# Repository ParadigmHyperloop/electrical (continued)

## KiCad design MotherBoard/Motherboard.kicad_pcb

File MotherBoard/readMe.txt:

Notes for Motherboard files.

*** Schematic ***
BBB headers will be shown true to pins because pinouts are not 
   set and updating the headers will be annoying.

Signals for MUX pins will be denoted with labels instead of wire 
   connections for flexibility and cleanliness.     

*** hyperLib ***
A and B designator for CD74HC4067 designate pinout orientation
   A is true to the physical pins, B is to show purpose/flow.

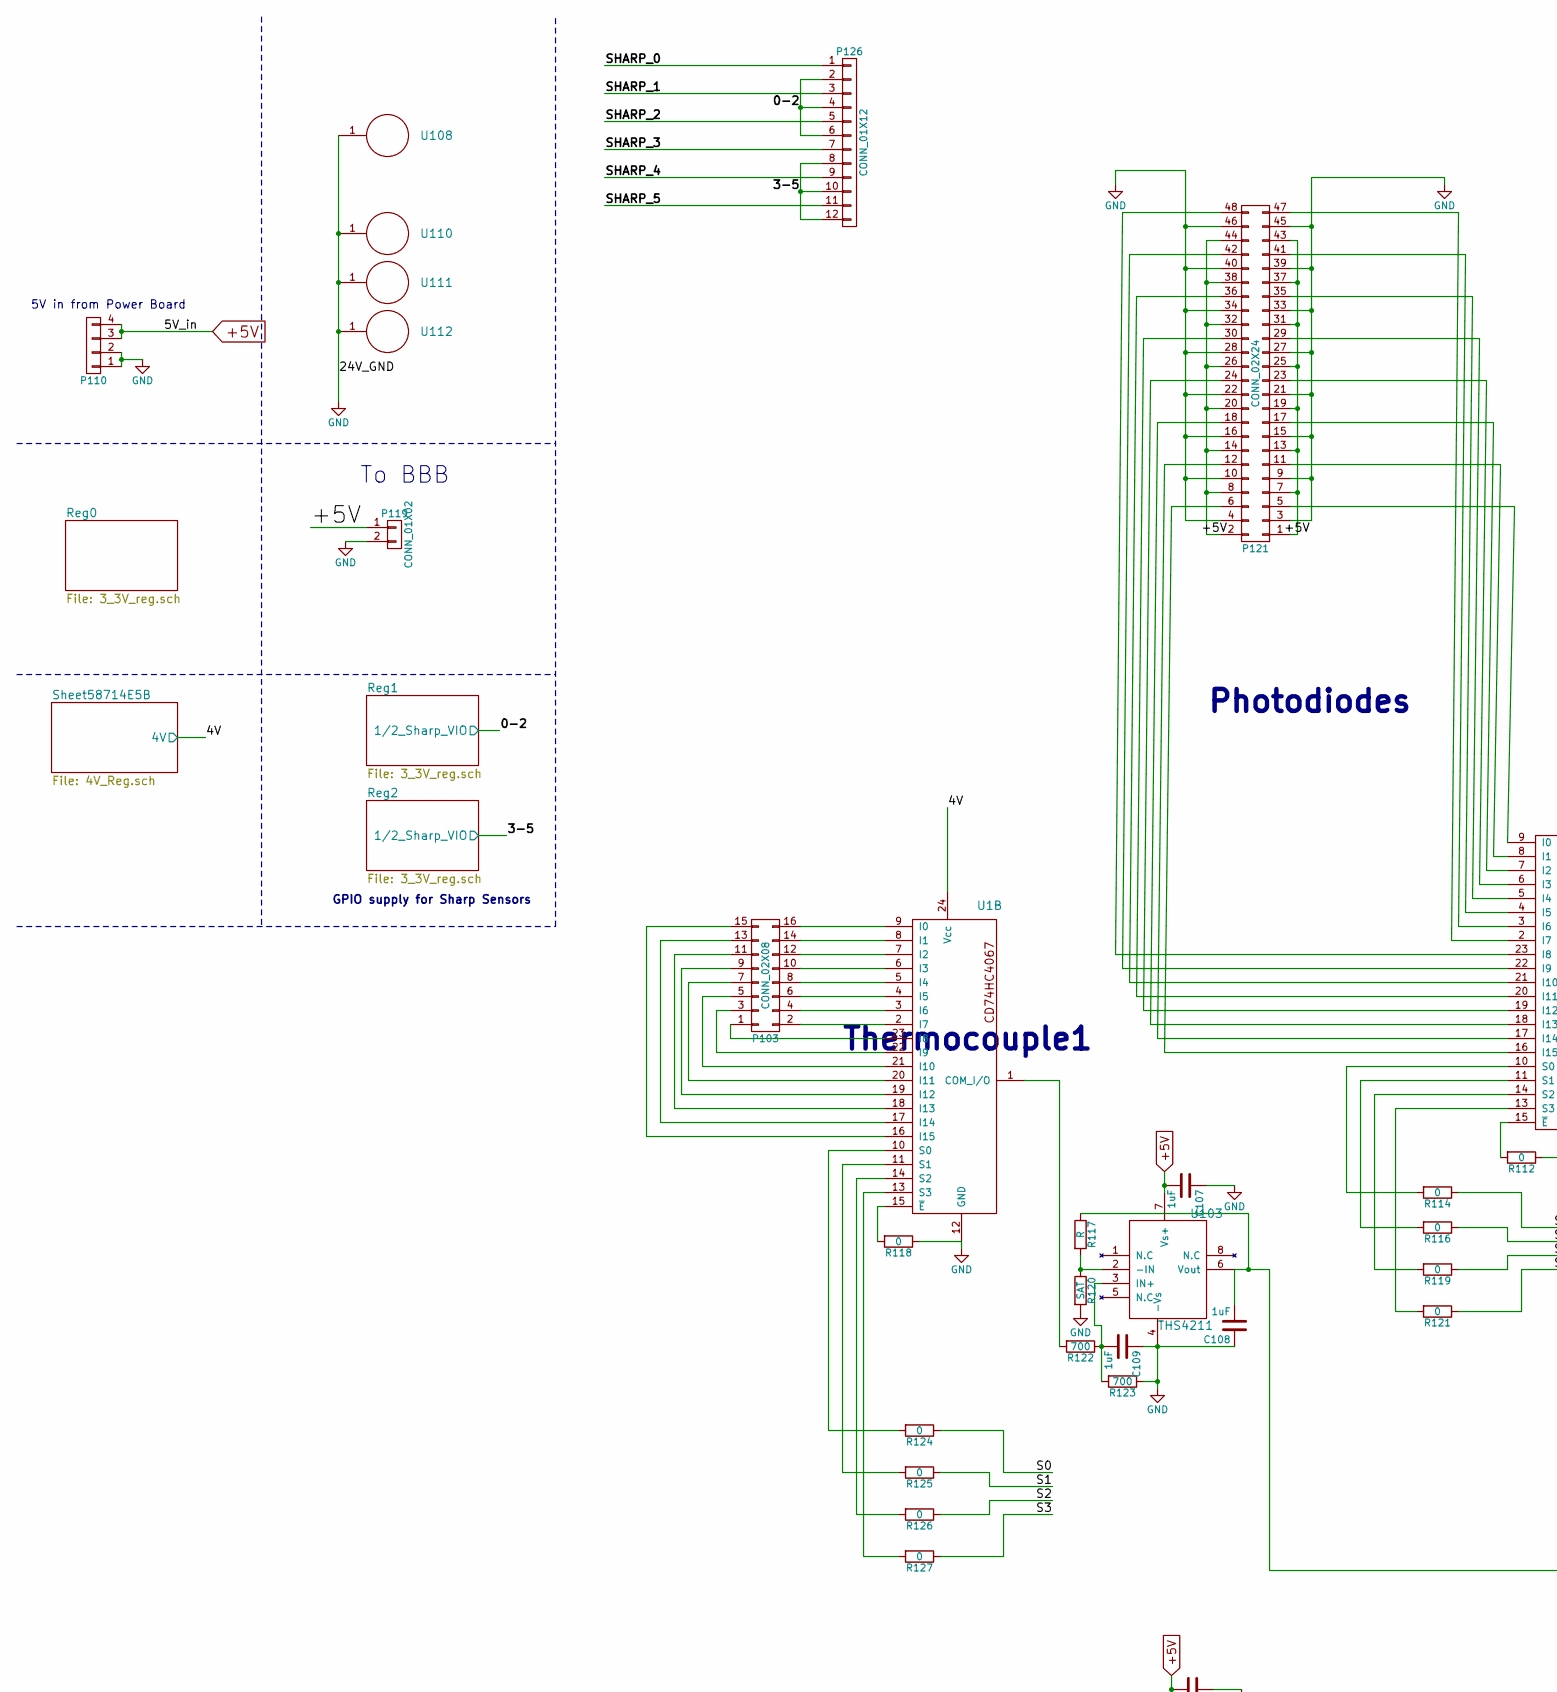
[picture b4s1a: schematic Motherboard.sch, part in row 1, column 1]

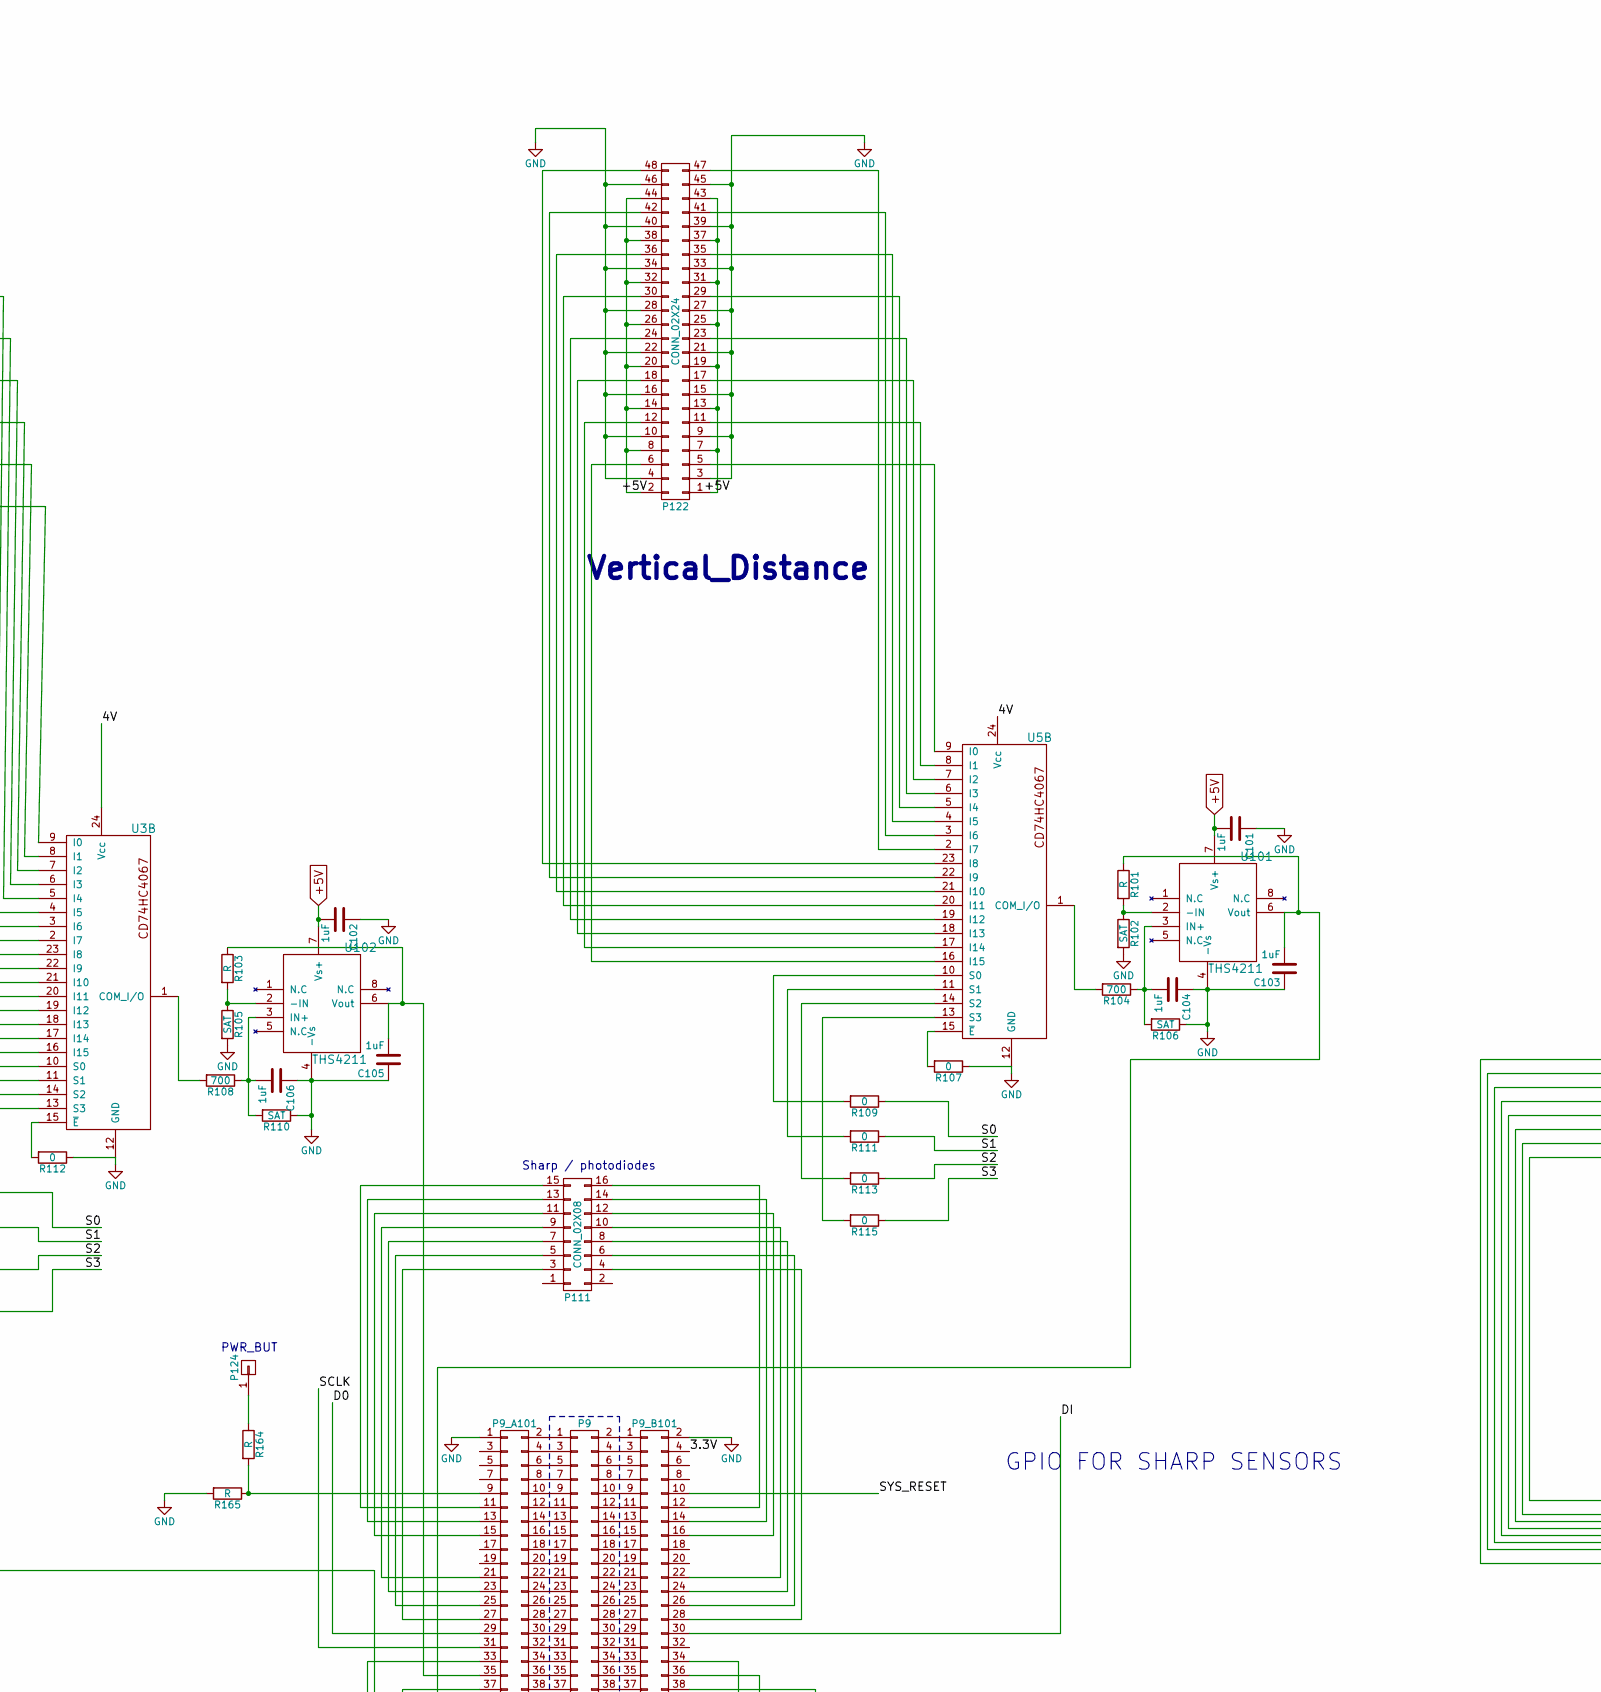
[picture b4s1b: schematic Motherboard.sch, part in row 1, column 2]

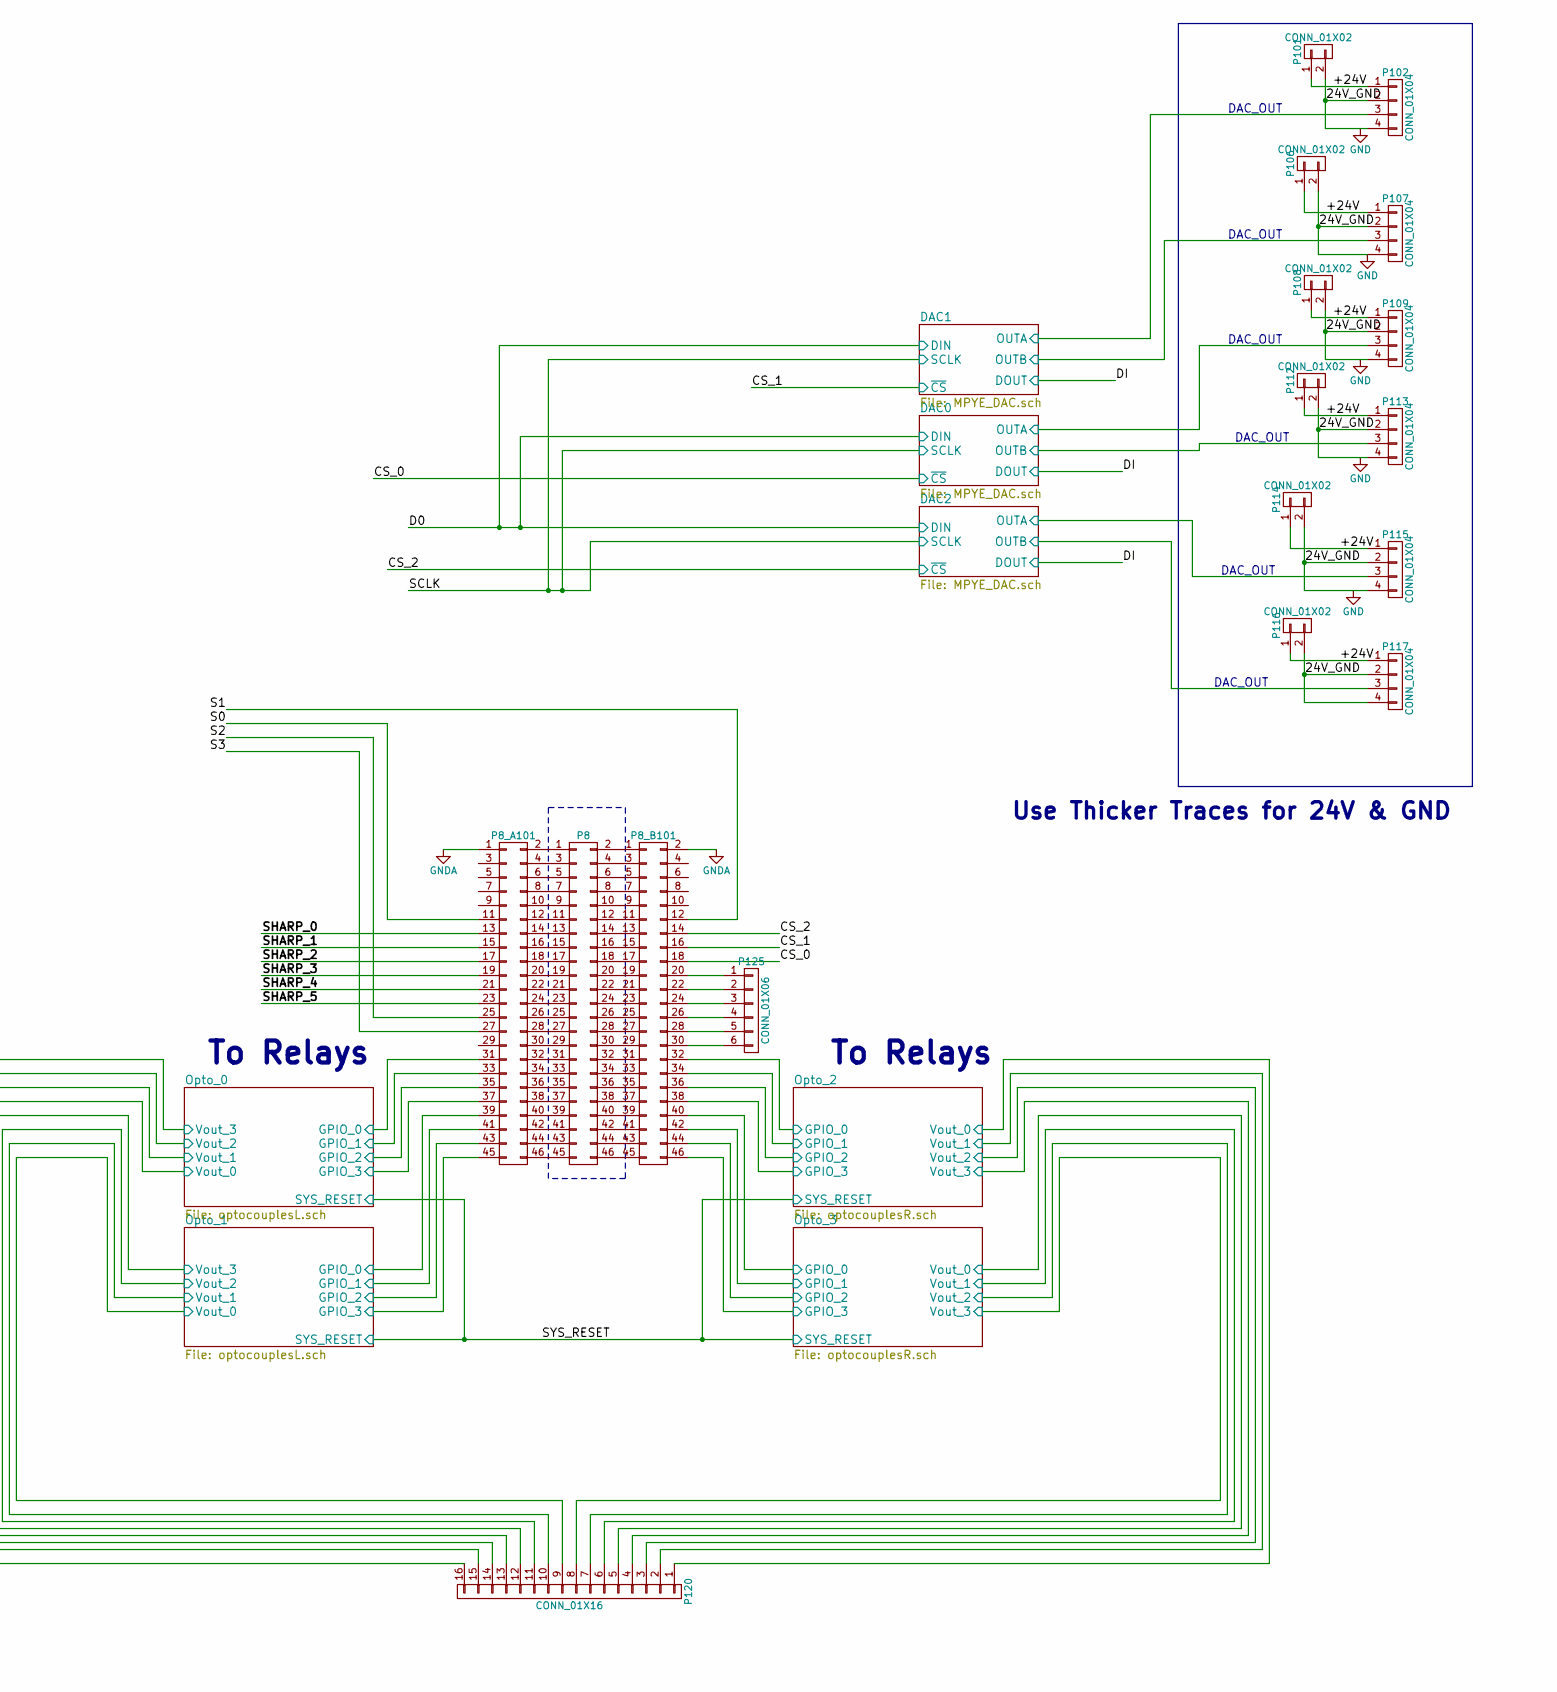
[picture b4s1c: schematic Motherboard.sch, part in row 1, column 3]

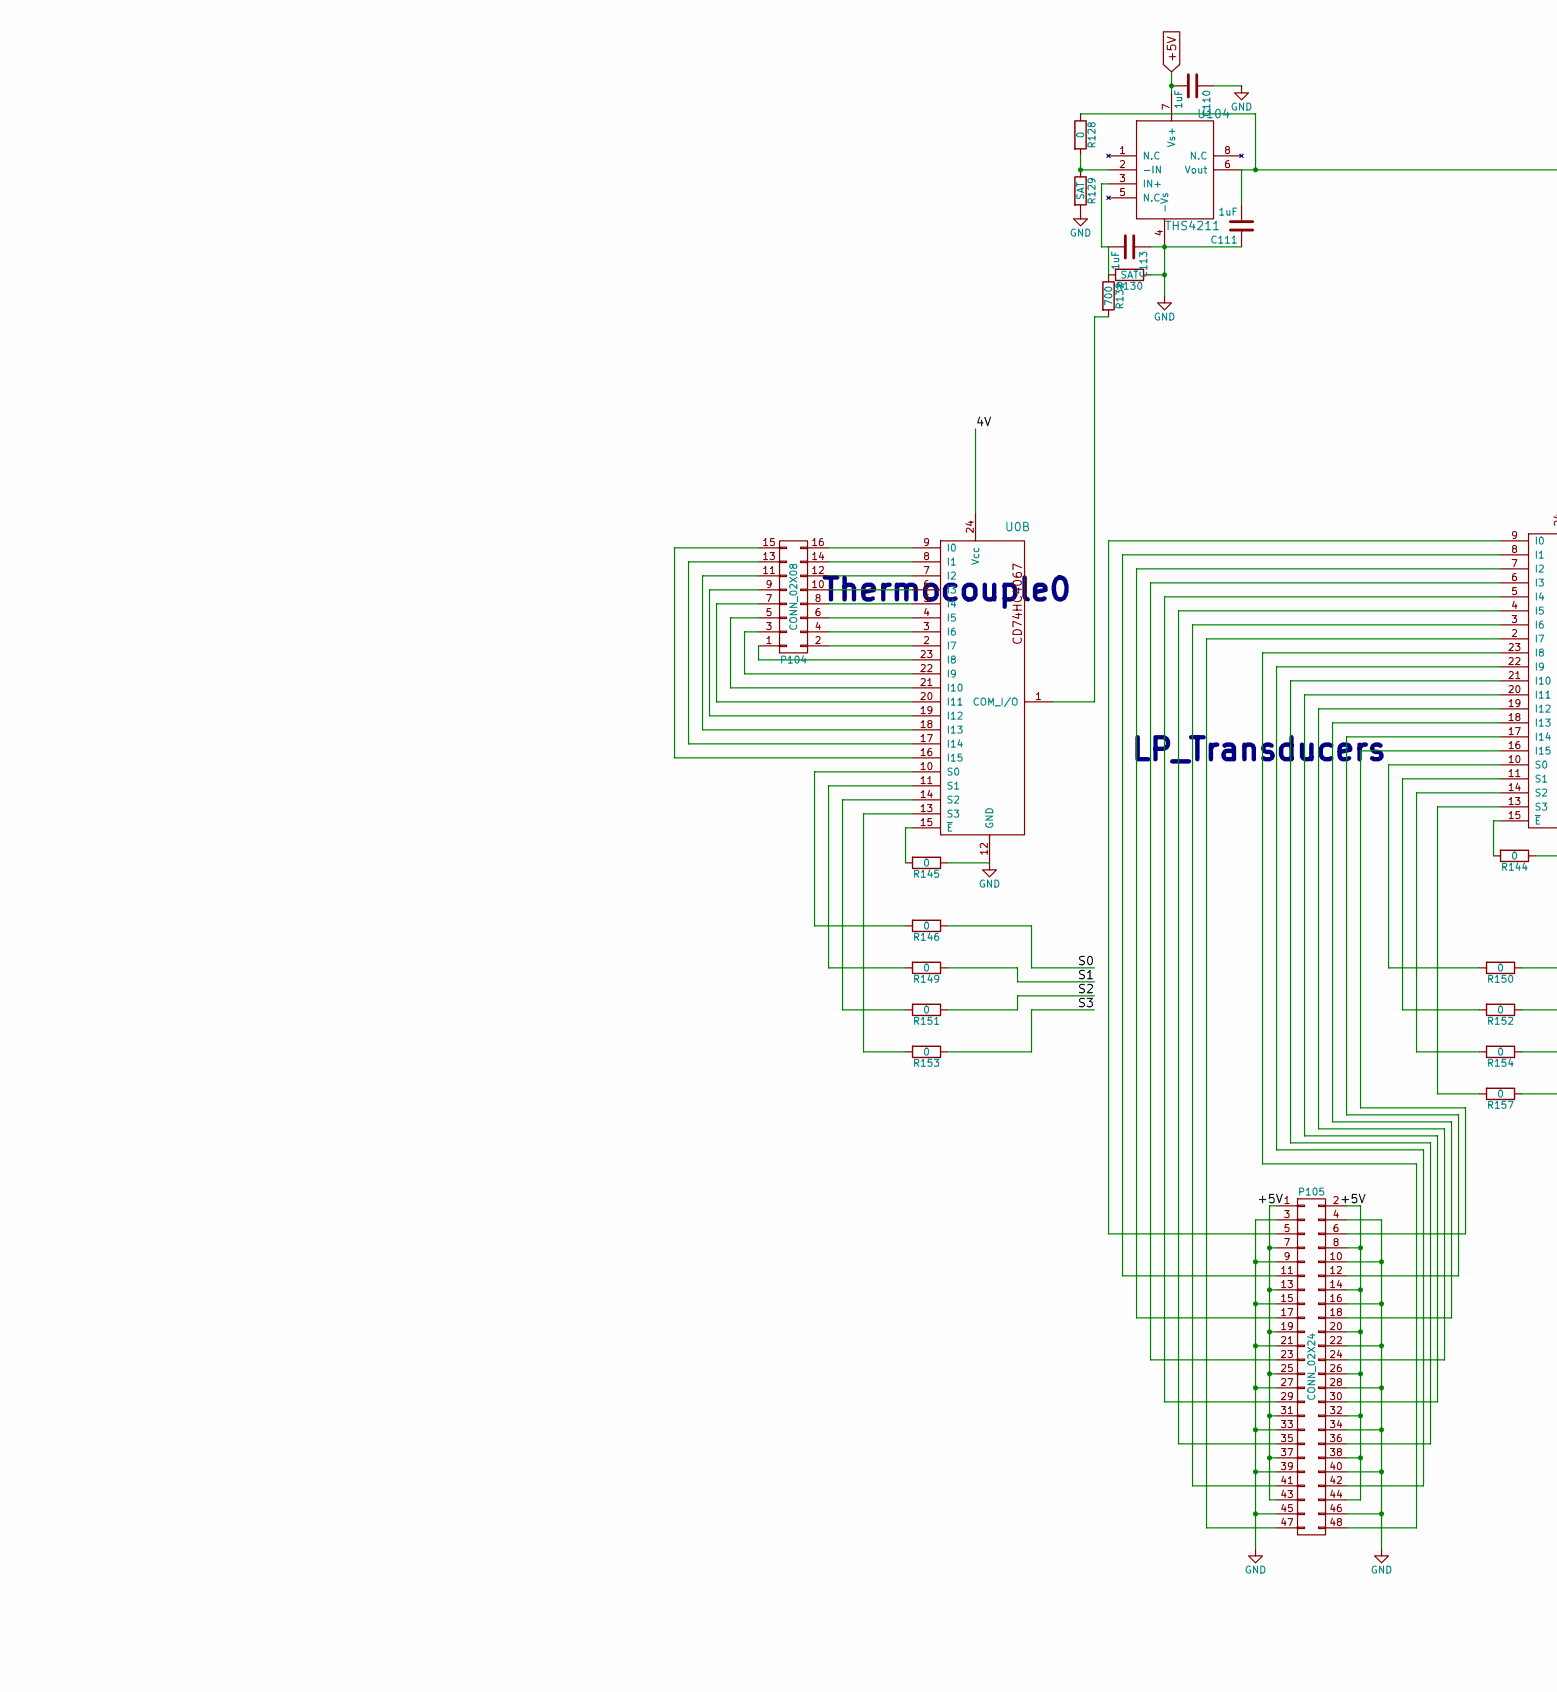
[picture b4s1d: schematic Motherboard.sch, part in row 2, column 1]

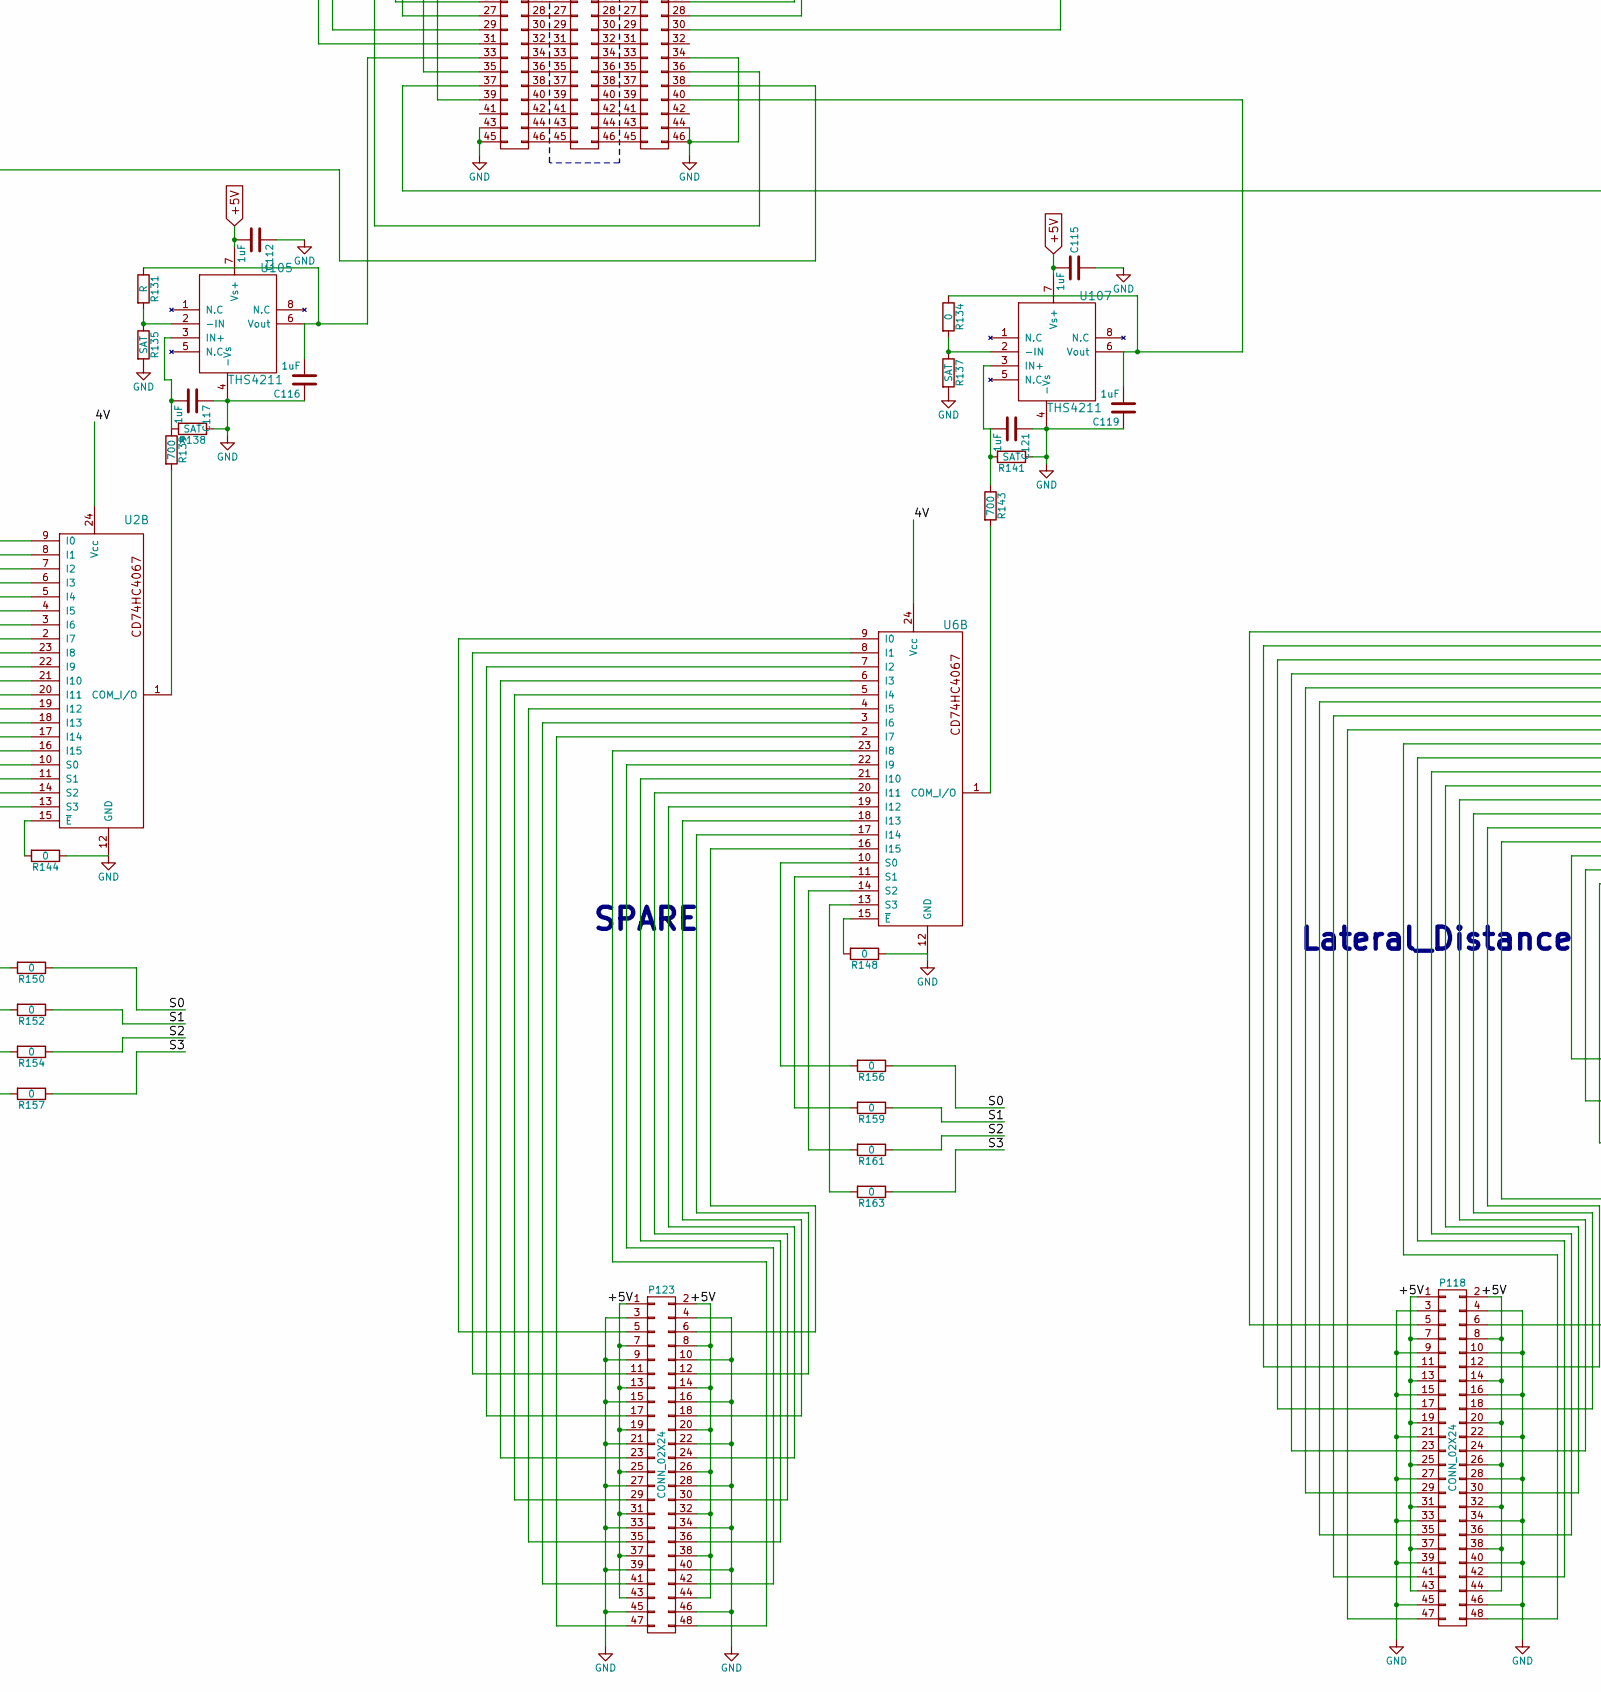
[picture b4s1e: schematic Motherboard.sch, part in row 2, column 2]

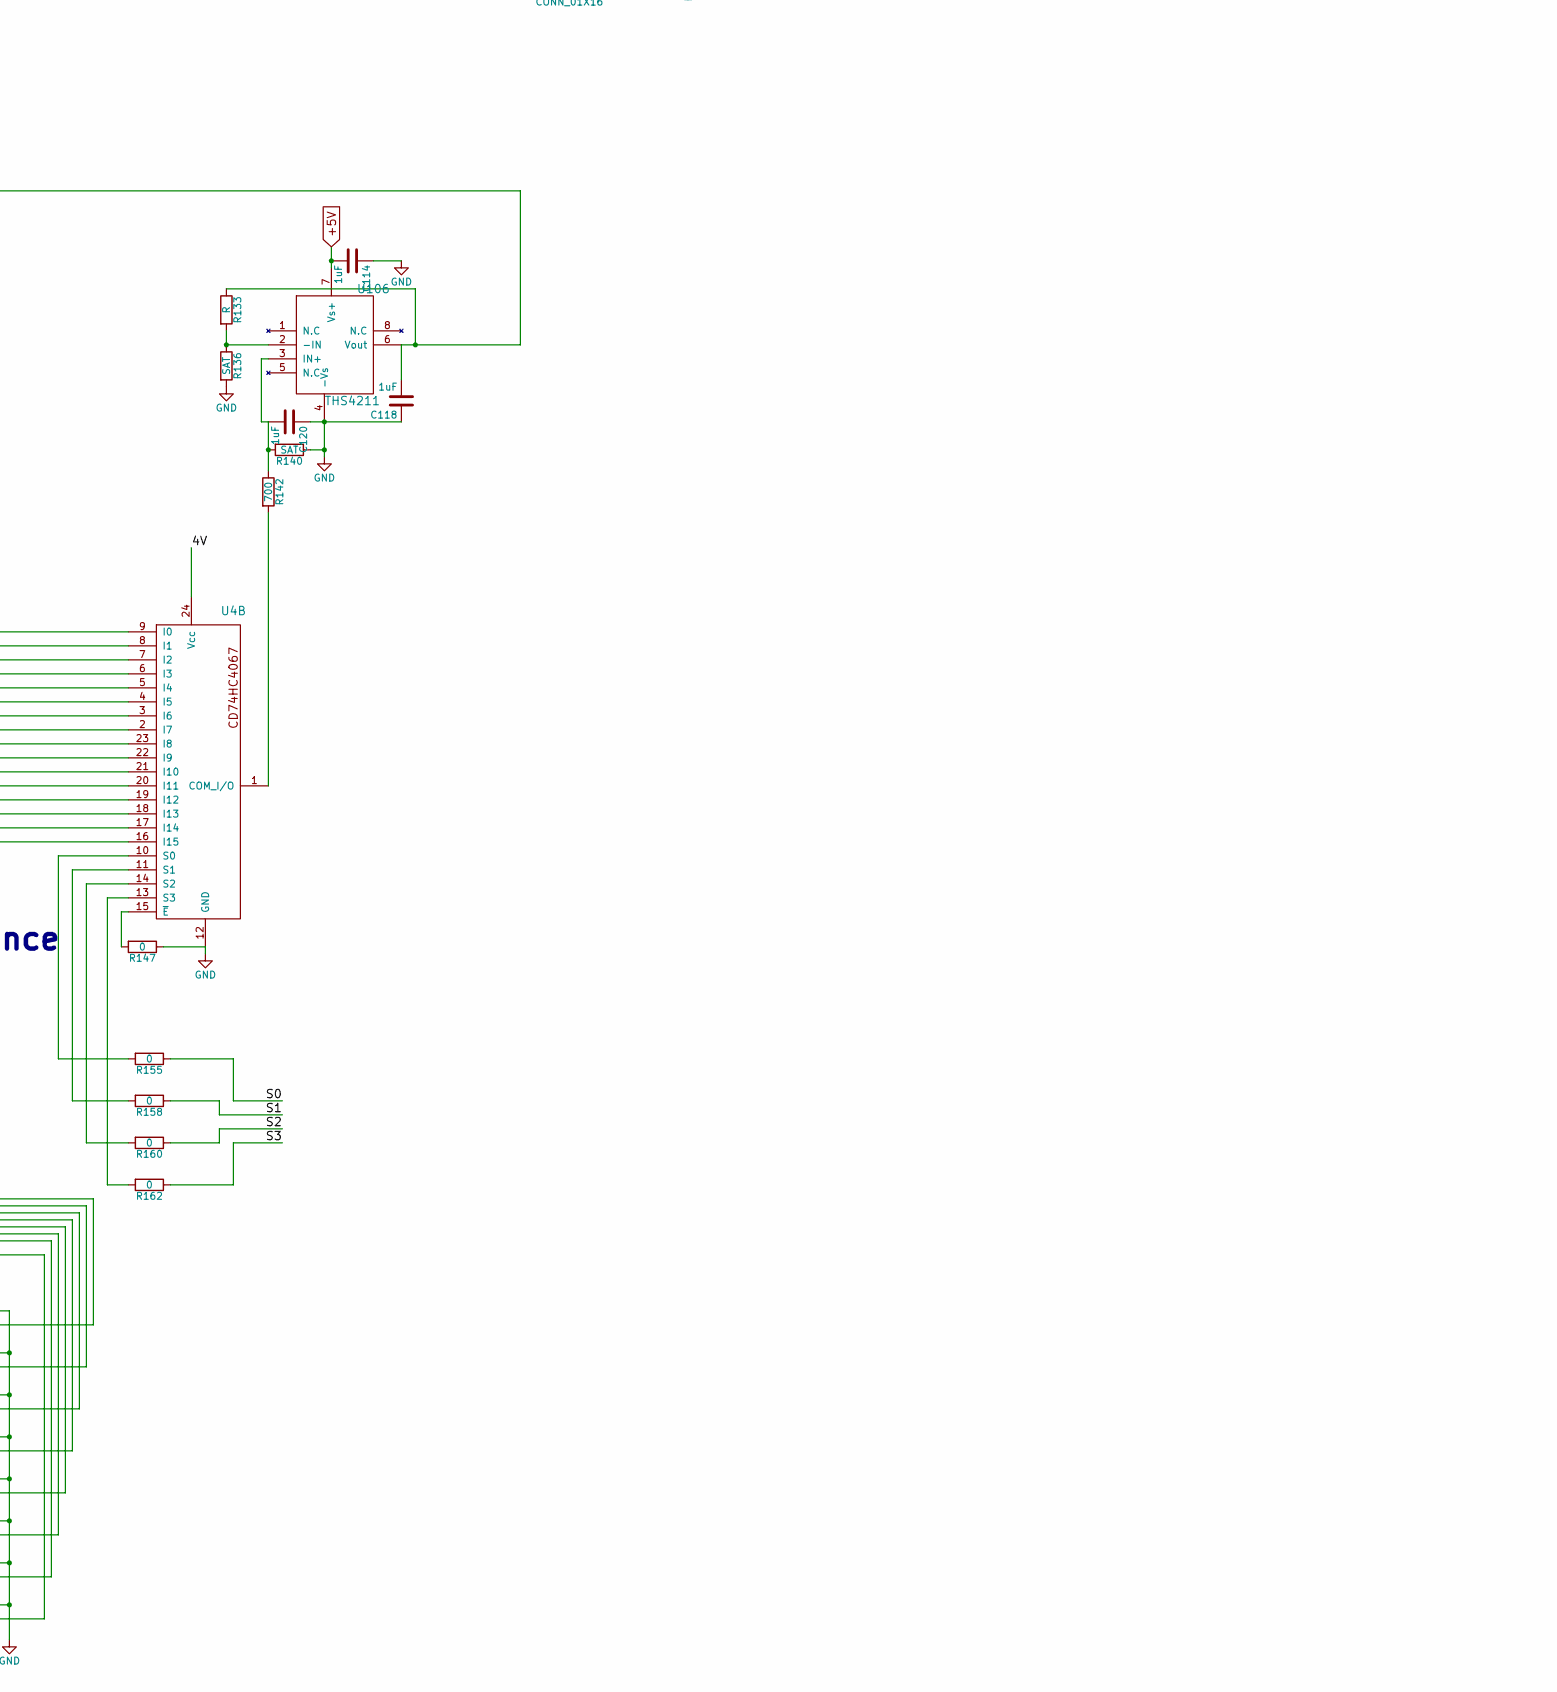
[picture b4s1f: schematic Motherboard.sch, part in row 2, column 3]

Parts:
C101, C102, C103, C104, C105, C106, C107, C108, C109, C110, C111, C112, C113, C114, C115, C116, C117, C118, C119, C120, C121: 1uF; C_0603_HandSoldering
P8, P8_A101, P8_B101: CONN_02X23; header_2.54x2.54mm_spacing_pinName
P9, P9_A101, P9_B101: CONN_02X23; header_2.54x2.54mm_spacing_pinName; Digikey P/N S2011E-23-ND
P101: CONN_01X02; TEconnectivity_2pin_screwTerminal; Digikey P/N A98333-ND
P102: CONN_01X04; pheonix_4pin_screwTerminal; Digikey P/N 277-1275-ND
P103, P104, P111: CONN_02X08; Molex_16pin_milliGrid; Digikey P/N WM18864-ND
P105, P118, P121, P122, P123: CONN_02X24; 02x48pin_2x2mm_Amphenol_header; Digikey P/N 609-2674-ND
P106, P108, P112, P114, P116: CONN_01X02; TEconnectivity_2pin_screwTerminal
P107: CONN_01X04; pheonix_4pin_screwTerminal; Digikey P/N 277-1275-Nd
P109, P110, P113, P115, P117: CONN_01X04; pheonix_4pin_screwTerminal
P119: CONN_01X02; SolderWirePad_2x_1mmDrill
P120: CONN_01X16; 16pin_screwTerminal; Digikey P/N 277-1733-ND
P124: CONN_01X01; 1pin
P125: CONN_01X06; CONN_01x06_standard
P126: CONN_01X12; 12pin_screwTerminal; Digikey P/N 277-1283-ND
R101, R103, R117, R131, R133, R164, R165: R; R_0603_HandSoldering
R102, R105, R106, R110, R120, R129, R130, R135, R136, R137, R138, R140, R141: SAT; R_0603_HandSoldering
R104, R108, R122, R123, R132, R139, R142, R143: 700; R_0603_HandSoldering
R107, R109, R111, R112, R113, R114, R115, R116, R118, R119, R121, R124, R125, R126, R127, R128, R134, R144, R145, R146, R147, R148, R149, R150, R151, R152, R153, R154, R155, R156, R157, R158, R159, R160, R161, R162, R163: 0; R_0603_HandSoldering
U0: CD74HC4067; SOIC-24W_7.5x15.4mm_Pitch1.27mm; Digikey P/N CD74HCT4067MG4-ND
U1, U2, U3, U4, U5, U6: CD74HC4067; SOIC-24W_7.5x15.4mm_Pitch1.27mm
U101, U102, U103, U104, U106, U107: THS4211; SOIC-8_3.9x4.9mm_Pitch1.27mm
U105: THS4211; SOIC-8_3.9x4.9mm_Pitch1.27mm; Digikey P/N 296-13790-5-ND
U108, U110, U111, U112: mounting_hole_5.5mm; MountingHole_5.5mm_Pad_Via

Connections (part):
/0-2: P126.2, P126.4, P126.6; also elsewhere on the board
/3-5: P126.8, P126.10, P126.12; also elsewhere on the board
/4V: U0.24 (Vcc), U1.24 (Vcc), U2.24 (Vcc), U3.24 (Vcc), U4.24 (Vcc), U5.24 (Vcc), U6.24 (Vcc); also elsewhere on the board
/+24V: P101.1, P102.1, P106.1, P107.1, P108.1, P109.1, P112.1, P113.1, P114.1, P115.1, P116.1, P117.1
/CS_0: P8_B101.18; also elsewhere on the board
/CS_1: P8_B101.16; also elsewhere on the board
/CS_2: P8_B101.14; also elsewhere on the board
/D0: P9_A101.29; also elsewhere on the board
/DAC0/OUTA: P109.3; also elsewhere on the board
/DAC0/OUTB: P113.3; also elsewhere on the board
/DAC1/OUTA: P102.3; also elsewhere on the board
/DAC1/OUTB: P107.3; also elsewhere on the board
/DAC2/OUTA: P115.3; also elsewhere on the board
/DAC2/OUTB: P117.3; also elsewhere on the board
/DI: P9_B101.30; also elsewhere on the board
/Opto_0/GPIO_0: P8_A101.31; also elsewhere on the board
/Opto_0/GPIO_1: P8_A101.33; also elsewhere on the board
/Opto_0/GPIO_2: P8_A101.35; also elsewhere on the board
/Opto_0/GPIO_3: P8_A101.37; also elsewhere on the board
/Opto_0/Vout_0: P120.13; also elsewhere on the board
/Opto_0/Vout_1: P120.14; also elsewhere on the board
/Opto_0/Vout_2: P120.15; also elsewhere on the board
/Opto_0/Vout_3: P120.16; also elsewhere on the board
/Opto_1/GPIO_0: P8_A101.39; also elsewhere on the board
/Opto_1/GPIO_1: P8_A101.41; also elsewhere on the board
/Opto_1/GPIO_2: P8_A101.43; also elsewhere on the board
/Opto_1/GPIO_3: P8_A101.45; also elsewhere on the board
/Opto_1/Vout_0: P120.9; also elsewhere on the board
/Opto_1/Vout_1: P120.10; also elsewhere on the board
/Opto_1/Vout_2: P120.11; also elsewhere on the board
/Opto_1/Vout_3: P120.12; also elsewhere on the board
/Opto_2/GPIO_0: P8_B101.32; also elsewhere on the board
/Opto_2/GPIO_1: P8_B101.34; also elsewhere on the board
/Opto_2/GPIO_2: P8_B101.36; also elsewhere on the board
/Opto_2/GPIO_3: P8_B101.38; also elsewhere on the board
/Opto_2/Vout_0: P120.1; also elsewhere on the board
/Opto_2/Vout_1: P120.2; also elsewhere on the board
/Opto_2/Vout_2: P120.3; also elsewhere on the board
/Opto_2/Vout_3: P120.4; also elsewhere on the board
/Opto_3/GPIO_0: P8_B101.40; also elsewhere on the board
/Opto_3/GPIO_1: P8_B101.42; also elsewhere on the board
/Opto_3/GPIO_2: P8_B101.44; also elsewhere on the board
/Opto_3/GPIO_3: P8_B101.46; also elsewhere on the board
/Opto_3/Vout_0: P120.5; also elsewhere on the board
/Opto_3/Vout_1: P120.6; also elsewhere on the board
/Opto_3/Vout_2: P120.7; also elsewhere on the board
/Opto_3/Vout_3: P120.8; also elsewhere on the board
/S0: P8_A101.11, R109.1, R114.1, R124.1, R146.1, R150.1, R155.1, R156.1
/S1: P8_B101.12, R111.1, R116.1, R125.1, R149.1, R152.1, R158.1, R159.1
/S2: P8_A101.25, R113.1, R119.1, R126.1, R151.1, R154.1, R160.1, R161.1
/S3: P8_A101.27, R115.1, R121.1, R127.1, R153.1, R157.1, R162.1, R163.1
/SCLK: P9_A101.31; also elsewhere on the board
/SHARP_0: P8_A101.13, P126.1
/SHARP_1: P8_A101.15, P126.3
/SHARP_2: P8_A101.17, P126.5
/SHARP_3: P8_A101.19, P126.7
/SHARP_4: P8_A101.21, P126.9
/SHARP_5: P8_A101.23, P126.11
/SYS_RESET: P9_B101.10; also elsewhere on the board
GND: C101.1, C102.1, C103.1, C104.1, C105.1, C106.1, C107.1, C108.1, C109.1, C110.1, C111.1, C112.1, C113.1, C114.1, C115.1, C116.1, C117.1, C118.1, C119.1, C120.1, C121.1, P9_A101.1, P9_A101.43, P9_A101.45, P9_B101.2, P9_B101.34, P9_B101.44, P9_B101.46, P101.2, P102.2, P102.4, P105.3, P105.4, P105.9, P105.10, P105.15, P105.16, P105.21, P105.22, P105.27, P105.28, P105.33, P105.34, P105.39, P105.40, P105.45, P105.46, P106.2, P107.2, P107.4, P108.2, P109.2, P109.4, P110.1, P110.2, P112.2, P113.2, P113.4, P114.2, P115.2, P115.4, P116.2, P117.2, P117.4, P118.3, P118.4, P118.9, P118.10, P118.15, P118.16, P118.21, P118.22, P118.27, P118.28, P118.33, P118.34, P118.39, P118.40, P118.45, P118.46, P119.2, P121.3, P121.4, P121.9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; also elsewhere on the board
GNDA: P8_A101.1, P8_B101.2
unnamed: C103.2, P9_A101.39, R101.1, U101.6 (Vout)
unnamed: C104.2, R104.1, R106.2, U101.3 (IN+)
unnamed: C105.2, P9_A101.35, R103.1, U102.6 (Vout)
unnamed: C106.2, R108.1, R110.2, U102.3 (IN+)
unnamed: C108.2, P9_B101.36, R117.1, U103.6 (Vout)
unnamed: C109.2, R122.1, R123.2, U103.3 (IN+)
unnamed: C111.2, P9_B101.38, R128.1, U104.6 (Vout)
unnamed: C113.2, R130.2, R132.1, U104.3 (IN+)
unnamed: C116.2, P9_A101.33, R131.1, U105.6 (Vout)
unnamed: C117.2, R138.2, R139.1, U105.3 (IN+)
unnamed: C118.2, P9_A101.37, R133.1, U106.6 (Vout)
unnamed: C119.2, P9_B101.40, R134.1, U107.6 (Vout)
unnamed: C120.2, R140.2, R142.1, U106.3 (IN+)
unnamed: C121.2, R141.2, R143.1, U107.3 (IN+)
unnamed: P8.1, P8_A101.2
unnamed: P8.2, P8_B101.1
unnamed: P8.3, P8_A101.4
unnamed: P8.4, P8_B101.3
unnamed: P8.5, P8_A101.6
unnamed: P8.6, P8_B101.5
unnamed: P8.7, P8_A101.8
unnamed: P8.8, P8_B101.7
unnamed: P8.9, P8_A101.10
unnamed: P8.10, P8_B101.9
unnamed: P8.11, P8_A101.12
unnamed: P8.12, P8_B101.11
unnamed: P8.13, P8_A101.14
unnamed: P8.14, P8_B101.13
unnamed: P8.15, P8_A101.16
unnamed: P8.16, P8_B101.15
unnamed: P8.17, P8_A101.18
unnamed: P8.18, P8_B101.17
unnamed: P8.19, P8_A101.20
unnamed: P8.20, P8_B101.19
unnamed: P8.21, P8_A101.22
unnamed: P8.22, P8_B101.21
unnamed: P8.23, P8_A101.24
unnamed: P8.24, P8_B101.23
unnamed: P8.25, P8_A101.26
unnamed: P8.26, P8_B101.25
unnamed: P8.27, P8_A101.28
unnamed: P8.28, P8_B101.27
unnamed: P8.29, P8_A101.30
unnamed: P8.30, P8_B101.29
unnamed: P8.31, P8_A101.32
unnamed: P8.32, P8_B101.31
unnamed: P8.33, P8_A101.34
unnamed: P8.34, P8_B101.33
unnamed: P8.35, P8_A101.36
unnamed: P8.36, P8_B101.35
unnamed: P8.37, P8_A101.38
unnamed: P8.38, P8_B101.37
unnamed: P8.39, P8_A101.40
unnamed: P8.40, P8_B101.39
unnamed: P8.41, P8_A101.42
unnamed: P8.42, P8_B101.41
unnamed: P8.43, P8_A101.44
unnamed: P8.44, P8_B101.43
unnamed: P8.45, P8_A101.46
unnamed: P8.46, P8_B101.45
unnamed: P9.1, P9_A101.2
unnamed: P9.2, P9_B101.1
unnamed: P9.3, P9_A101.4
unnamed: P9.4, P9_B101.3
unnamed: P9.5, P9_A101.6
unnamed: P9.6, P9_B101.5
unnamed: P9.7, P9_A101.8
unnamed: P9.8, P9_B101.7
unnamed: P9.9, P9_A101.10
unnamed: P9.10, P9_B101.9
unnamed: P9.11, P9_A101.12
unnamed: P9.12, P9_B101.11
unnamed: P9.13, P9_A101.14
unnamed: P9.14, P9_B101.13
unnamed: P9.15, P9_A101.16
unnamed: P9.16, P9_B101.15
unnamed: P9.17, P9_A101.18
unnamed: P9.18, P9_B101.17
unnamed: P9.19, P9_A101.20
unnamed: P9.20, P9_B101.19
unnamed: P9.21, P9_A101.22
unnamed: P9.22, P9_B101.21
unnamed: P9.23, P9_A101.24
unnamed: P9.24, P9_B101.23
unnamed: P9.25, P9_A101.26
unnamed: P9.26, P9_B101.25
unnamed: P9.27, P9_A101.28
unnamed: P9.28, P9_B101.27
unnamed: P9.29, P9_A101.30
unnamed: P9.30, P9_B101.29
unnamed: P9.31, P9_A101.32
unnamed: P9.32, P9_B101.31
unnamed: P9.33, P9_A101.34
unnamed: P9.34, P9_B101.33
unnamed: P9.35, P9_A101.36
unnamed: P9.36, P9_B101.35
unnamed: P9.37, P9_A101.38
unnamed: P9.38, P9_B101.37
unnamed: P9.39, P9_A101.40
unnamed: P9.40, P9_B101.39
unnamed: P9.41, P9_A101.42
unnamed: P9.42, P9_B101.41
unnamed: P9.43, P9_A101.44
unnamed: P9.44, P9_B101.43
unnamed: P9.45, P9_A101.46
unnamed: P9.46, P9_B101.45
unnamed: P9_A101.9, R164.2, R165.1
unnamed: P103.1, U1.23 (I8)
unnamed: P103.2, U1.2 (I7)
unnamed: P103.3, U1.22 (I9)
unnamed: P103.4, U1.3 (I6)
unnamed: P103.5, U1.21 (I10)
unnamed: P103.6, U1.4 (I5)
unnamed: P103.7, U1.20 (I11)
unnamed: P103.8, U1.5 (I4)
unnamed: P103.9, U1.19 (I12)
unnamed: P103.10, U1.6 (I3)
unnamed: P103.11, U1.18 (I13)
unnamed: P103.12, U1.7 (I2)
unnamed: P103.13, U1.17 (I14)
unnamed: P103.14, U1.8 (I1)
unnamed: P103.15, U1.16 (I15)
unnamed: P103.16, U1.9 (I0)
unnamed: P104.1, U0.23 (I8)
unnamed: P104.2, U0.2 (I7)
unnamed: P104.3, U0.22 (I9)
unnamed: P104.4, U0.3 (I6)
unnamed: P104.5, U0.21 (I10)
unnamed: P104.6, U0.4 (I5)
unnamed: P104.7, U0.20 (I11)
unnamed: P104.8, U0.5 (I4)
unnamed: P104.9, U0.19 (I12)
unnamed: P104.10, U0.6 (I3)
unnamed: P104.11, U0.18 (I13)
unnamed: P104.12, U0.7 (I2)
unnamed: P104.13, U0.17 (I14)
unnamed: P104.14, U0.8 (I1)
unnamed: P104.15, U0.16 (I15)
unnamed: P104.16, U0.9 (I0)
unnamed: P105.1, P105.7, P105.13, P105.19, P105.25, P105.31, P105.37, P105.43
unnamed: P105.5, U2.9 (I0)
unnamed: P105.6, U2.16 (I15)
unnamed: P105.11, U2.8 (I1)
unnamed: P105.12, U2.17 (I14)
unnamed: P105.2, P105.8, P105.14, P105.20, P105.26, P105.32, P105.38, P105.44
unnamed: P105.17, U2.7 (I2)
unnamed: P105.18, U2.18 (I13)
unnamed: P105.23, U2.6 (I3)
unnamed: P105.24, U2.19 (I12)
unnamed: P105.29, U2.5 (I4)
unnamed: P105.30, U2.20 (I11)
unnamed: P105.35, U2.4 (I5)
unnamed: P105.36, U2.21 (I10)
unnamed: P105.41, U2.3 (I6)
unnamed: P105.42, U2.22 (I9)
unnamed: P105.47, U2.2 (I7)
unnamed: P105.48, U2.23 (I8)
unnamed: P9_A101.27, P111.3
unnamed: P9_B101.28, P111.4
unnamed: P9_A101.25, P111.5
unnamed: P9_B101.26, P111.6
unnamed: P9_A101.23, P111.7
unnamed: P9_B101.24, P111.8
unnamed: P9_A101.21, P111.9
unnamed: P9_B101.22, P111.10
unnamed: P9_A101.15, P111.11
unnamed: P9_B101.16, P111.12
unnamed: P9_A101.13, P111.13
unnamed: P9_B101.14, P111.14
unnamed: P9_A101.11, P111.15
unnamed: P9_B101.12, P111.16
unnamed: P118.1, P118.7, P118.13, P118.19, P118.25, P118.31, P118.37, P118.43
unnamed: P118.5, U4.9 (I0)
unnamed: P118.6, U4.16 (I15)
unnamed: P118.11, U4.8 (I1)
unnamed: P118.12, U4.17 (I14)
unnamed: P118.2, P118.8, P118.14, P118.20, P118.26, P118.32, P118.38, P118.44
unnamed: P118.17, U4.7 (I2)
unnamed: P118.18, U4.18 (I13)
unnamed: P118.23, U4.6 (I3)
unnamed: P118.24, U4.19 (I12)
unnamed: P118.29, U4.5 (I4)
unnamed: P118.30, U4.20 (I11)
unnamed: P118.35, U4.4 (I5)
unnamed: P118.36, U4.21 (I10)
unnamed: P118.41, U4.3 (I6)
unnamed: P118.42, U4.22 (I9)
unnamed: P118.47, U4.2 (I7)
unnamed: P118.48, U4.23 (I8)
unnamed: P121.1, P121.7, P121.13, P121.19, P121.25, P121.31, P121.37, P121.43
unnamed: P121.5, U3.9 (I0)
unnamed: P121.6, U3.16 (I15)
unnamed: P121.11, U3.8 (I1)
unnamed: P121.12, U3.17 (I14)
unnamed: P121.2, P121.8, P121.14, P121.20, P121.26, P121.32, P121.38, P121.44
unnamed: P121.17, U3.7 (I2)
unnamed: P121.18, U3.18 (I13)
unnamed: P121.23, U3.6 (I3)
unnamed: P121.24, U3.19 (I12)
unnamed: P121.29, U3.5 (I4)
unnamed: P121.30, U3.20 (I11)
unnamed: P121.35, U3.4 (I5)
unnamed: P121.36, U3.21 (I10)
unnamed: P121.41, U3.3 (I6)
unnamed: P121.42, U3.22 (I9)
unnamed: P121.47, U3.2 (I7)
unnamed: P121.48, U3.23 (I8)
unnamed: P122.1, P122.7, P122.13, P122.19, P122.25, P122.31, P122.37, P122.43
unnamed: P122.5, U5.9 (I0)
unnamed: P122.6, U5.16 (I15)
unnamed: P122.11, U5.8 (I1)
unnamed: P122.12, U5.17 (I14)
unnamed: P122.2, P122.8, P122.14, P122.20, P122.26, P122.32, P122.38, P122.44
unnamed: P122.17, U5.7 (I2)
unnamed: P122.18, U5.18 (I13)
unnamed: P122.23, U5.6 (I3)
unnamed: P122.24, U5.19 (I12)
unnamed: P122.29, U5.5 (I4)
unnamed: P122.30, U5.20 (I11)
unnamed: P122.35, U5.4 (I5)
unnamed: P122.36, U5.21 (I10)
unnamed: P122.41, U5.3 (I6)
unnamed: P122.42, U5.22 (I9)
unnamed: P122.47, U5.2 (I7)
unnamed: P122.48, U5.23 (I8)
unnamed: P123.1, P123.7, P123.13, P123.19, P123.25, P123.31, P123.37, P123.43
unnamed: P123.5, U6.9 (I0)
unnamed: P123.6, U6.16 (I15)
unnamed: P123.11, U6.8 (I1)
unnamed: P123.12, U6.17 (I14)
unnamed: P123.2, P123.8, P123.14, P123.20, P123.26, P123.32, P123.38, P123.44
unnamed: P123.17, U6.7 (I2)
unnamed: P123.18, U6.18 (I13)
unnamed: P123.23, U6.6 (I3)
unnamed: P123.24, U6.19 (I12)
unnamed: P123.29, U6.5 (I4)
unnamed: P123.30, U6.20 (I11)
unnamed: P123.35, U6.4 (I5)
unnamed: P123.36, U6.21 (I10)
unnamed: P123.41, U6.3 (I6)
unnamed: P123.42, U6.22 (I9)
unnamed: P123.47, U6.2 (I7)
unnamed: P123.48, U6.23 (I8)
unnamed: P124.1, R164.1
unnamed: P8_B101.20, P125.1
unnamed: P8_B101.22, P125.2
unnamed: P8_B101.24, P125.3
unnamed: P8_B101.26, P125.4
unnamed: P8_B101.28, P125.5
unnamed: P8_B101.30, P125.6
unnamed: R101.2, R102.1, U101.2 (-IN)
unnamed: R103.2, R105.1, U102.2 (-IN)
unnamed: R104.2, U5.1 (COM_I/O)
unnamed: R107.2, U5.15 (~E~)
unnamed: R108.2, U3.1 (COM_I/O)
unnamed: R109.2, U5.10 (S0)
unnamed: R111.2, U5.11 (S1)
unnamed: R112.2, U3.15 (~E~)
unnamed: R113.2, U5.14 (S2)
unnamed: R114.2, U3.10 (S0)
unnamed: R115.2, U5.13 (S3)
unnamed: R116.2, U3.11 (S1)
unnamed: R117.2, R120.1, U103.2 (-IN)
unnamed: R118.2, U1.15 (~E~)
unnamed: R119.2, U3.14 (S2)
unnamed: R121.2, U3.13 (S3)
unnamed: R122.2, U1.1 (COM_I/O)
unnamed: R124.2, U1.10 (S0)
unnamed: R125.2, U1.11 (S1)
unnamed: R126.2, U1.14 (S2)
unnamed: R127.2, U1.13 (S3)
unnamed: R128.2, R129.1, U104.2 (-IN)
unnamed: R131.2, R135.1, U105.2 (-IN)
unnamed: R132.2, U0.1 (COM_I/O)
unnamed: R133.2, R136.1, U106.2 (-IN)
unnamed: R134.2, R137.1, U107.2 (-IN)
unnamed: R139.2, U2.1 (COM_I/O)
unnamed: R142.2, U4.1 (COM_I/O)
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
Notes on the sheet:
Thermocouple1
To Relays
DAC_OUT
5V in from Power Board
Lateral_Distance
SPARE
Thermocouple0
GPIO FOR SHARP SENSORS
To BBB
Vertical_Distance
Photodiodes
LP_Transducers
Use Thicker Traces for 24V & GND
PWR_BUT
Sharp / photodiodes
GPIO supply for Sharp Sensors
